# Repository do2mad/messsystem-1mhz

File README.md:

# Messsystem 6× DC + 1× AC

Ein kleines Messgerät für den Reparaturplatz: Es überwacht **sechs
Gleichspannungen (0–30 V)** und **eine Wechselspannung (9 V~)** gleichzeitig
und zeigt sie auf einem **20×4-LCD** an. Entstanden ist es, um die
Spannungsschienen eines Commodore-64 , Pet oder andere in einem Blick zu prüfen —
es passt aber auf jedes Gerät mit mehreren Versorgungsspannungen.

Projektseite und Diskussion: <https://1mhz.de>

*Startbild mit Firmware-Version. Unten die Eingänge: +5 V/GND/AC, DC1–DC6 als Klemmen und DC6 zusätzlich an 2-mm-Bananenbuchsen (J16).*

*Im Betrieb: zwei belegte Kanäle, die übrigen ausgeblendet. Rechts unten zeigt `UEBERW`, dass die Grenzwert-Überwachung aktiv ist.*

## Was es kann

- **7 Kanäle an einem ADC**: ein CD4051 schaltet die Eingänge auf einen
  einzigen ADC-Pin, ein MCP6004-Spannungsfolger entkoppelt den hochohmigen
  Teiler vom Sample-and-Hold.
- **Grenzwert-Überwachung**: Ein funktionierendes Gerät anschließen, Taste
  halten, Toleranz wählen — fertig. Fällt am Prüfling eine Schiene aus dem
  Bereich, meldet sich das Gerät mit Ton, blinkendem Hintergrundlicht und
  einem blinkenden Kanal im Display.
- **Kalibrierung mit zwei Punkten pro Kanal**, im EEPROM gespeichert.
- **Datenaufzeichnung** als CSV über die serielle Schnittstelle, mit
  Semikolon und Dezimalkomma — direkt in der Tabellenkalkulation brauchbar.
- **Serielle Konsole** für Kalibrierung, Grenzwerte und Diagnose.

## Technik in Stichworten

| | |
|---|---|
| MCU | ATmega328P, interner 8-MHz-Oszillator, kein Quarz |
| Multiplexer | CD4051 (8:1) auf ADC0 (PC0) |
| Puffer | MCP6004 (Rail-to-Rail, pinkompatibel zum LM324, **max. 6 V**) |
| Referenz | LM4040 4,096 V an AREF |
| Anzeige | HD44780 20×4, parallel im 4-Bit-Modus |
| DC-Eingänge | Teiler 1 MΩ / 100 kΩ (≈1:11), 100 nF, bipolare 1N4148-Klemme |
| AC-Eingang | Brückengleichrichter, Teiler 470 k / 150 k, Mittelwert → `Vrms = MW / 0,9` |
| Alarm | passiver Piezo (Reichelt EPM 121, 4 kHz) gegentaktig an PB6/PB7 über 330 Ω; Hintergrundlicht über Q1 (2N7000) an PB3 |
| Versorgung | 5 V über J9 oder USB-Mini J10 (nur eine Quelle gleichzeitig, kein Verpolschutz) |

## Bedienung

**Taster SW1 im Betrieb**

| Aktion | Wirkung |
|---|---|
| kurz tippen | Alarm stumm, bis er vorbei ist |
| ≥ 2 s halten | Grenzen einrichten, startet bei ± 1 % |
| im Einrichten tippen | Toleranz +1 % je Tipp (1…20, dann wieder 1) |
| im Einrichten 5 s warten | einlernen mit der gezeigten Toleranz, Wert wird gespeichert |
| ≥ 6 s halten | alle Grenzen löschen |
| beim Einschalten halten | Kalibriermodus |

Das Statusfeld unten rechts zeigt `UEBERW`, `ALARM!`, `STUMM`, beim Halten
`SETUP` bzw. `LOESCH` und im Einrichten die Toleranz, etwa `+- 7%`.

**Summer dauerhaft aus:** Jumper am ISP-Stecker J18 über Pin 1 und 3
(MISO gegen SCK). Zum Programmieren muss er ohnehin herunter.

**Serielle Konsole** (9600 Baud, `?` zeigt die Liste):
`l` Aufzeichnung · `r` Rohwerte · `s` Stopp · `1`–`6` / `a` kalibrieren ·
`g` / `G` Grenzen anzeigen/setzen · `e` einlernen · `t` Toleranz ·
`x` löschen · `m` stumm · `b` Summer-Test

## Firmware bauen und flashen

Arduino-IDE mit **MiniCore**: Board „ATmega328", Variante 328P,
Clock **Internal 8 MHz**, *No bootloader* → „Kompilierte Binärdatei
exportieren". Bibliothek `LiquidCrystal` ist im Core enthalten.

Fuses beim Brennen (z. B. TL866-II Plus, Xgpro, ATMEGA328P@DIP28):

```
Low = 0xE2    High = 0xD9    Ext = 0xFF   (0xFD für Brown-out 2,7 V)
```

Nach dem ersten Flashen einmal kalibrieren: beim Einschalten den Taster
gedrückt halten.

## Hardware

Das KiCad-Projekt liegt unter `hardware/kicad/` und bringt **alle benutzten
Symbole und Footprints als Projektbibliothek** mit (`libs/`, eingebunden über
`sym-lib-table` und `fp-lib-table`). Es lässt sich also ohne zusätzliche
Bibliotheken öffnen und bearbeiten. KiCad 10.

Die 3D-Modelle liegen vollständig in `hardware/kicad/packages3D/` – die
3D-Ansicht (Alt+3) ist nach dem Klonen sofort komplett, ohne weitere
Downloads.

Stückliste: `hardware/BOM.md` (mit Erklärungen) und `hardware/BOM.csv`.

## Stand

Aufgebaut, bestückt und im Einsatz. Die Versionsgeschichte mit allen
Entscheidungen, Messungen und Fallstricken steht in `CHANGELOG.md` —
auch die Geschichte vom gefälschten LM4040.

## Lizenz

MIT, siehe `LICENSE`. Nachbau, Änderung und Weitergabe sind ausdrücklich
erwünscht — über eine Rückmeldung im Forum freue ich mich.

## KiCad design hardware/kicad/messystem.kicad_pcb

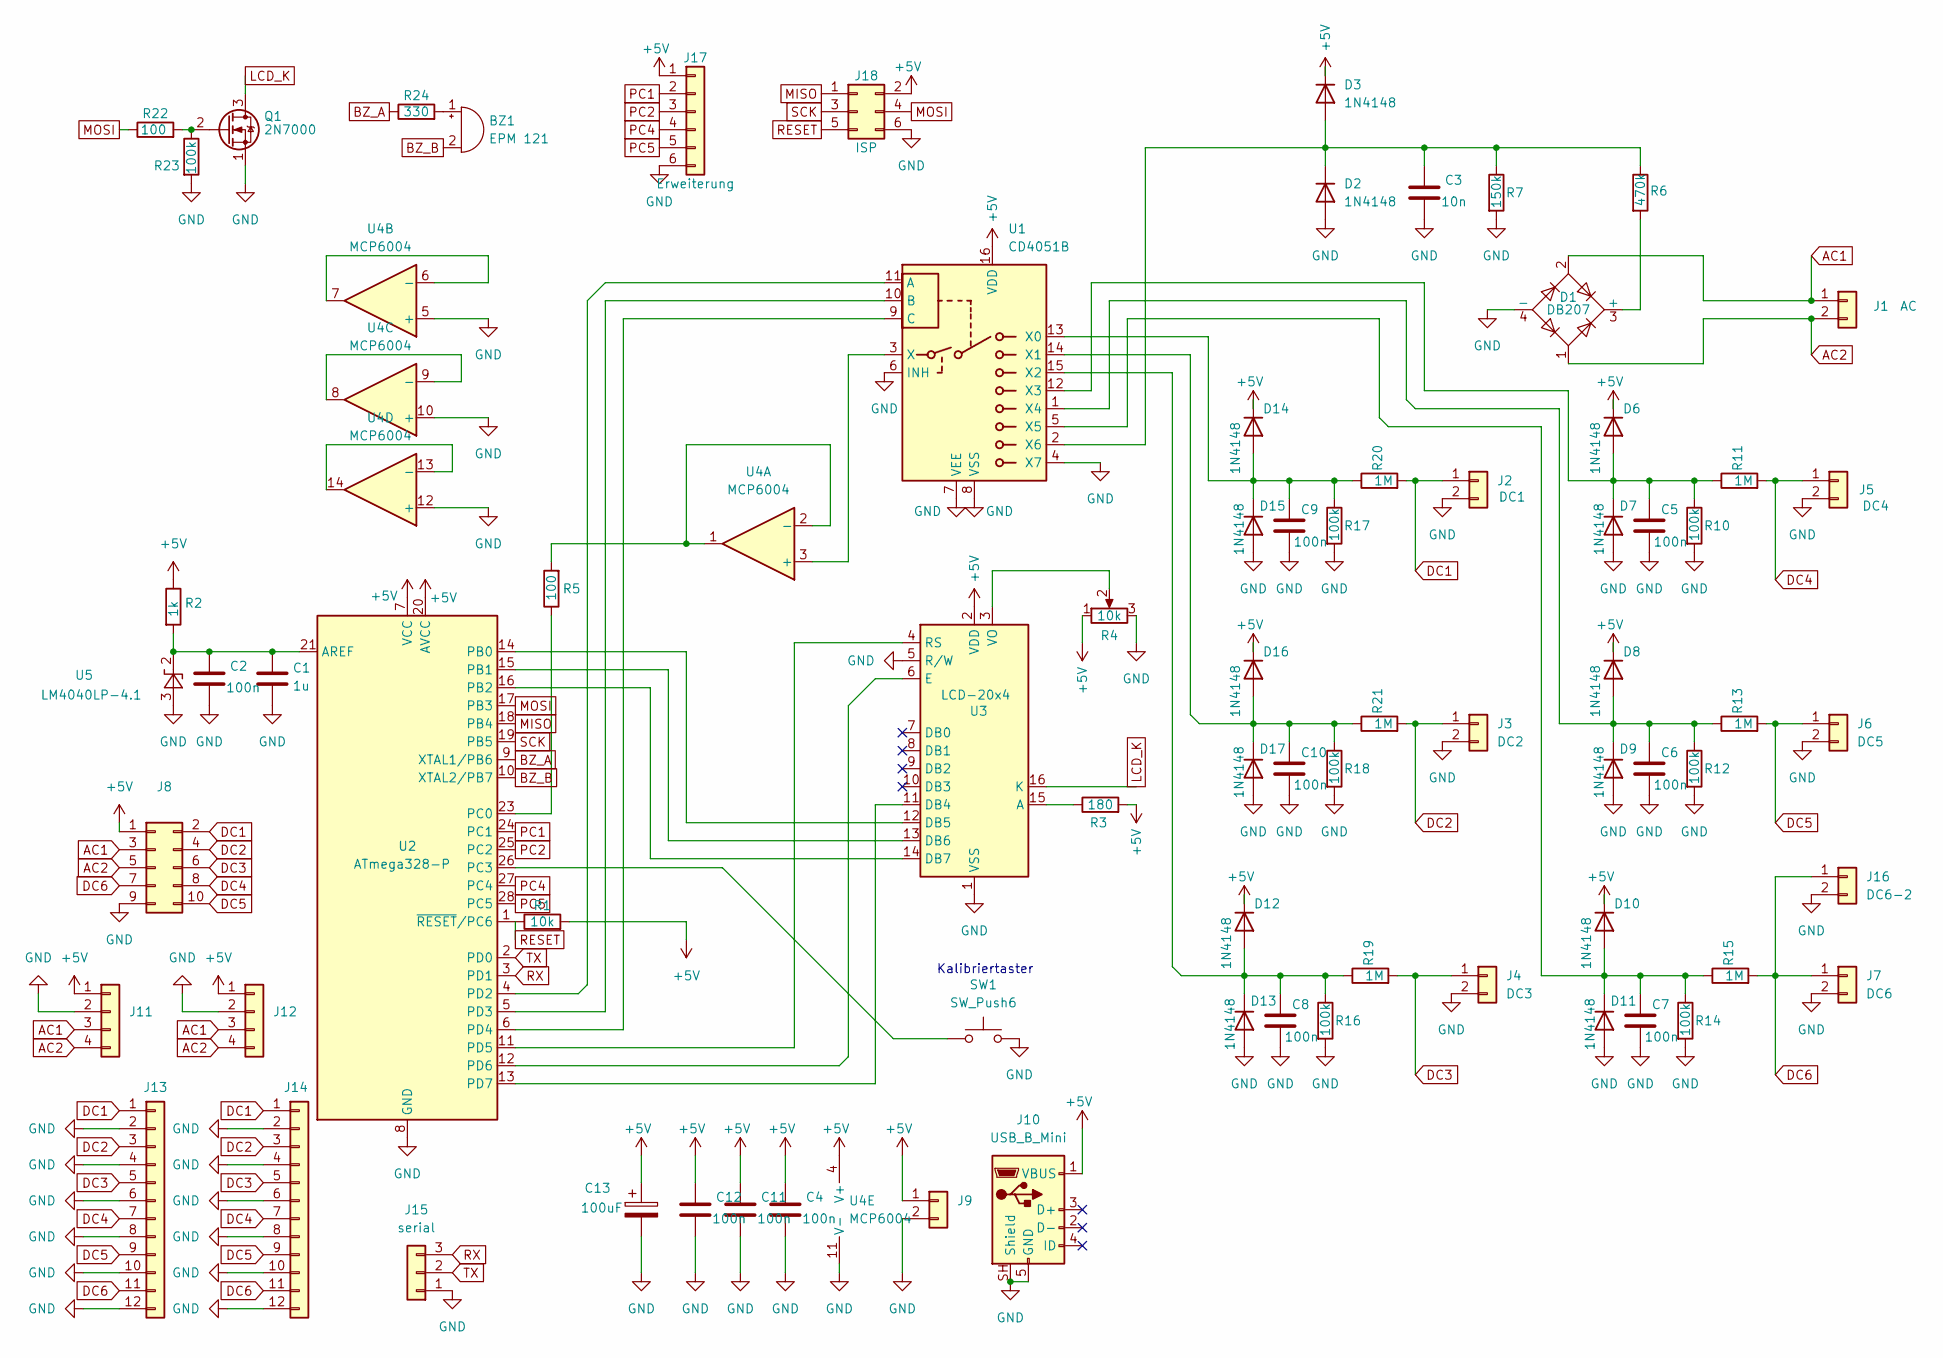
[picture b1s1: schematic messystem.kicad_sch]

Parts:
BZ1: EPM 121; Buzzer_12x9.5RM7.6
C1: 1u; C_MAD
C2, C4, C5, C6, C7, C8, C9, C10, C11, C12: 100n; C_MAD
C3: 10n; C_MAD
C13: 100uF; Elko_Mad
D1: DB207; Diode_Bridge_DIP-4_W7.62mm_P5.08mm
D2, D3, D6, D7, D8, D9, D10, D11, D12, D13, D14, D15, D16, D17: 1N4148; D_DO-35_SOD27_P7.62mm_Horizontal
J1: AC; PinHeader_1x02_P2.54mm_Vertical-MAD
J2: DC1; PinHeader_1x02_P2.54mm_Vertical-MAD
J3: DC2; PinHeader_1x02_P2.54mm_Vertical-MAD
J4: DC3; PinHeader_1x02_P2.54mm_Vertical-MAD
J5: DC4; PinHeader_1x02_P2.54mm_Vertical-MAD
J6: DC5; PinHeader_1x02_P2.54mm_Vertical-MAD
J7: DC6; PinHeader_1x02_P2.54mm_Vertical-MAD
J8: Conn_02x05_Odd_Even; IDC-Header_2x05_P2.54mm_Horizontal
J9: 5V; PinHeader_1x02_P2.54mm_Vertical-MAD
J10: USB_B_Mini; USB_Mini-B_horizontal
J11, J12: 5V/AC; PinSocket_1x04_P2.54mm_Vertical
J13, J14: DC1-DC6; PinSocket_1x12_P2.54mm_Vertical
J15: serial; PinSocket_1x03_P2.54mm_Vertical
J16: DC6-2; 2mm-banane
J17: Erweiterung; PinHeader_1x06_P2.54mm_Vertical
J18: ISP; PinHeader_2x03_P2.54mm_Vertical
Q1: 2N7000; TO-92_Inline
R1: 10k; R_Axial_DIN0204_L3.6mm_D1.6mm_P7.62mm_Horizontal
R2: 1k; R_Axial_DIN0204_L3.6mm_D1.6mm_P7.62mm_Horizontal
R3: 180; R_Axial_DIN0204_L3.6mm_D1.6mm_P7.62mm_Horizontal
R4: 10k; Potentiometer_Bourns_3296W_Vertical
R5, R22: 100; R_Axial_DIN0204_L3.6mm_D1.6mm_P7.62mm_Horizontal
R6: 470k; R_Axial_DIN0204_L3.6mm_D1.6mm_P7.62mm_Horizontal
R7: 150k; R_Axial_DIN0204_L3.6mm_D1.6mm_P7.62mm_Horizontal
R10, R12, R14, R16, R17, R18, R23: 100k; R_Axial_DIN0204_L3.6mm_D1.6mm_P7.62mm_Horizontal
R11, R13, R15, R19, R20, R21: 1M; R_Axial_DIN0204_L3.6mm_D1.6mm_P7.62mm_Horizontal
R24: 330; R_Axial_DIN0204_L3.6mm_D1.6mm_P7.62mm_Horizontal
SW1: SW_Push6; SW_Tactile_SPST_Angled_PTS645Vx39-2LFS
U1: CD4051B; DIP-16_W7.62mm_Socket_LongPads
U2: ATmega328-P; DIP-28_W7.62mm
U3: LCD-20x4
U4: MCP6004; DIP-14_W7.62mm_LongPads
U5: LM4040LP-4.1; TO-92_Inline

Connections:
+5V: C4.1, C11.1, C12.1, C13.1, D3.1 (K), D6.1 (K), D8.1 (K), D10.1 (K), D12.1 (K), D14.1 (K), D16.1 (K), J8.1, J9.1, J10.1 (VBUS), J11.1, J12.1, J17.1, J18.2, R1.2, R2.1, R3.2, R4.1, U1.16 (VDD), U2.7 (VCC), U2.20 (AVCC), U3.2 (VDD), U4.4 (V+)
AC1: D1.2, J1.1, J8.3, J11.3, J12.3
AC2: D1.1, J1.2, J8.5, J11.4, J12.4
BZ_A: R24.1, U2.9 (XTAL1/PB6)
BZ_B: BZ1.2 (-), U2.10 (XTAL2/PB7)
DC1: J2.1, J8.2, J13.1, J14.1, R20.2
DC2: J3.1, J8.4, J13.3, J14.3, R21.2
DC3: J4.1, J8.6, J13.5, J14.5, R19.2
DC4: J5.1, J8.8, J13.7, J14.7, R11.2
DC5: J6.1, J8.10, J13.9, J14.9, R13.2
DC6: J7.1, J8.7, J13.11, J14.11, J16.1, R15.2
GND: C1.2, C2.2, C3.2, C4.2, C5.2, C6.2, C7.2, C8.2, C9.2, C10.2, C11.2, C12.2, C13.2, D1.4 (-), D2.2 (A), D7.2 (A), D9.2 (A), D11.2 (A), D13.2 (A), D15.2 (A), D17.2 (A), J2.2, J3.2, J4.2, J5.2, J6.2, J7.2, J8.9, J9.2, J10.5 (GND), J10.SH (Shield), J11.2, J12.2, J13.2, J13.4, J13.6, J13.8, J13.10, J13.12, J14.2, J14.4, J14.6, J14.8, J14.10, J14.12, J15.1, J16.2, J17.6, J18.6, Q1.1 (S), R4.3, R7.2, R10.2, R12.2, R14.2, R16.2, R17.2, R18.2, R23.2, SW1.2, U1.4 (X7), U1.6 (INH), U1.7 (VEE), U1.8 (VSS), U2.8 (GND), U2.22 (GND), U3.1 (VSS), U3.5 (R/W), U3.17, U3.18, U3.19, U3.20, U4.5 (+), U4.10 (+), U4.11 (V-), U4.12 (+), U5.3 (A)
LCD_K: Q1.3 (D), U3.16 (K)
MISO: J18.1, U2.18 (PB4)
MOSI: J18.4, R22.1, U2.17 (PB3)
unnamed: BZ1.1 (+), R24.2
unnamed: D1.3 (+), R6.2
unnamed: C3.1, D2.1 (K), D3.2 (A), R6.1, R7.1, U1.2 (X6)
unnamed: C5.1, D6.2 (A), D7.1 (K), R10.1, R11.1, U1.12 (X3)
unnamed: C6.1, D8.2 (A), D9.1 (K), R12.1, R13.1, U1.1 (X4)
unnamed: C7.1, D10.2 (A), D11.1 (K), R14.1, R15.1, U1.5 (X5)
unnamed: C8.1, D12.2 (A), D13.1 (K), R16.1, R19.1, U1.15 (X2)
unnamed: C9.1, D14.2 (A), D15.1 (K), R17.1, R20.1, U1.13 (X0)
unnamed: C10.1, D16.2 (A), D17.1 (K), R18.1, R21.1, U1.14 (X1)
unnamed: Q1.2 (G), R22.2, R23.1
unnamed: U1.11 (A), U2.4 (PD2)
unnamed: U1.10 (B), U2.5 (PD3)
unnamed: U1.9 (C), U2.6 (PD4)
unnamed: U1.3 (X), U4.3 (+)
unnamed: C1.1, C2.1, R2.2, U2.21 (AREF), U5.2 (K)
unnamed: U2.14 (PB0), U3.12 (DB5)
unnamed: U2.15 (PB1), U3.13 (DB6)
unnamed: U2.16 (PB2), U3.14 (DB7)
unnamed: R5.1, U2.23 (PC0)
unnamed: SW1.1, U2.26 (PC3)
unnamed: U2.11 (PD5), U3.4 (RS)
unnamed: U2.12 (PD6), U3.6 (E)
unnamed: U2.13 (PD7), U3.11 (DB4)
unnamed: R3.1, U3.15 (A)
unnamed: R4.2, U3.3 (VO)
unnamed: R5.2, U4.1, U4.2 (-)
unnamed: U4.6 (-), U4.7
unnamed: U4.8, U4.9 (-)
unnamed: U4.13 (-), U4.14
PC1: J17.2, U2.24 (PC1)
PC2: J17.3, U2.25 (PC2)
PC4: J17.4, U2.27 (PC4)
PC5: J17.5, U2.28 (PC5)
RESET: J18.5, R1.1, U2.1 (~RESET/PC6)
RX: J15.3, U2.3 (PD1)
SCK: J18.3, U2.19 (PB5)
TX: J15.2, U2.2 (PD0)

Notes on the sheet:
Kalibriertaster

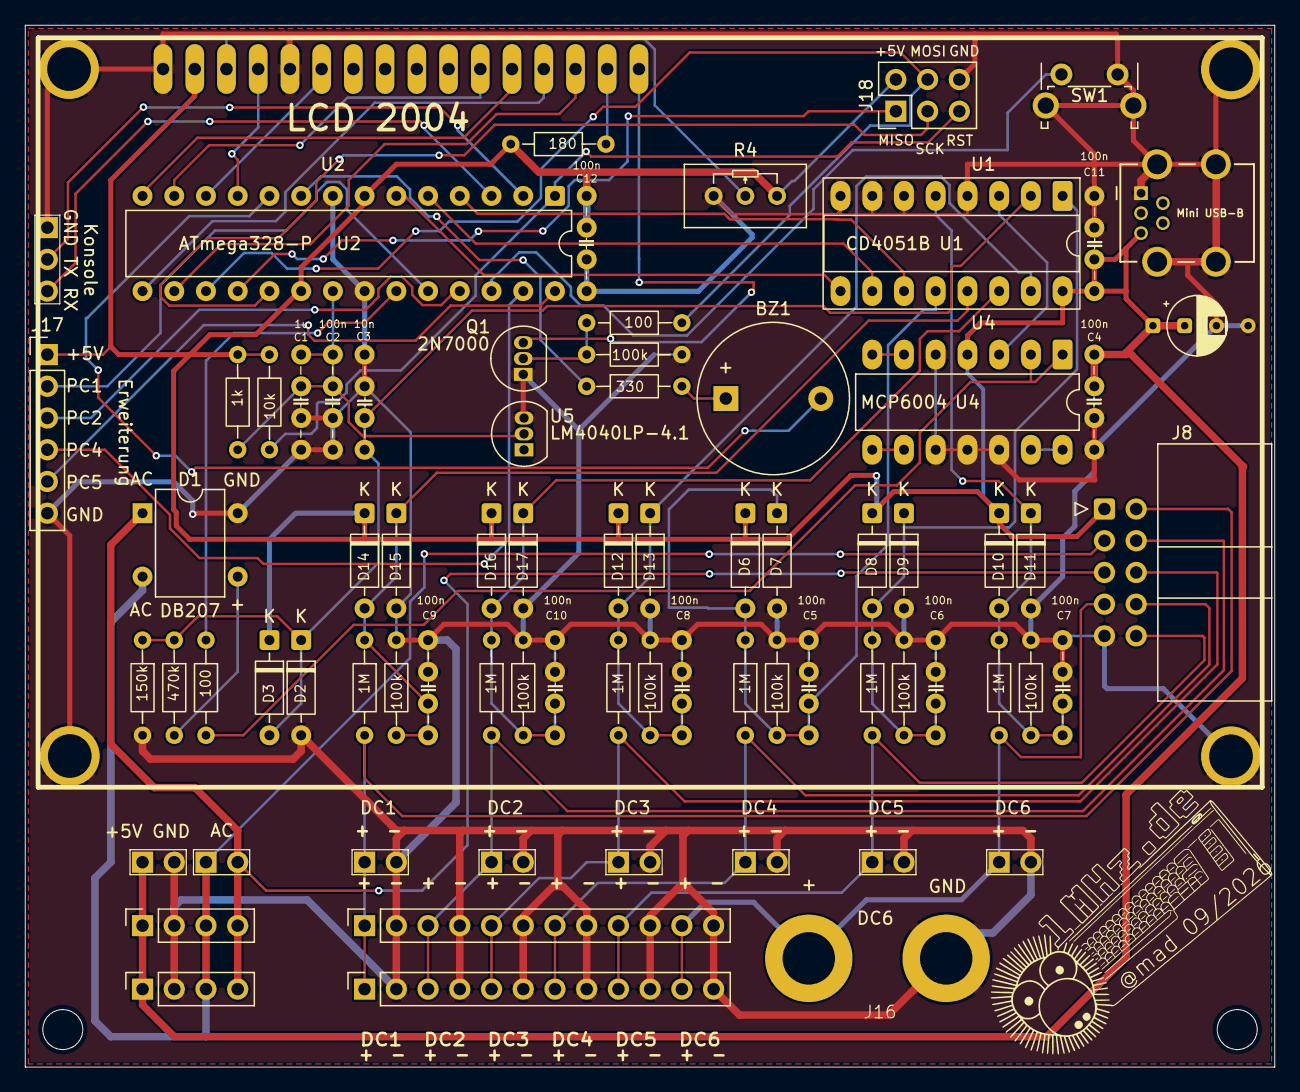
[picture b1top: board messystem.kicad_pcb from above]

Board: 2 copper layers, 100.0 x 83.4 mm, 78 parts (1 on the bottom side), 52 nets.

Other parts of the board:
1MHZ, 1MHZ.de: LOGO; 1MHzLogo25

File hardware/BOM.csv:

Menge;Bezeichner;Bauteil;Wert;Gehaeuse;Funktion
1;U1;CD4051BE;;DIP-16;8:1 Analog-Mux
1;U2;ATmega328P-PU;;DIP-28;MCU (int. 8 MHz)
1;U3;LCD 20x4 HD44780;;Modul parallel;Display + 16-pol Leiste
1;U4;MCP6004;;DIP-14;Quad-OpAmp RRIO, Sektion A = Follower, max. 6 V
1;U5;LM4040DIZ-4.1;4,096 V;TO-92;Spannungsreferenz (Test: LM4040-2.5)
1;D1;Brueckengleichrichter;;KONFLIKT;Value MB6S (SOP-4) vs. Footprint Diode_Bridge_DIP-4 - klaeren
14;D2,D3,D6-D17;1N4148;;DO-35;bipolare Klemmdioden (2x je Kanal)
1;R1;Widerstand;10k;0207;Reset-Pullup
1;R2;Widerstand;1k;0207;Vorwiderstand Referenz U5
1;R3;Widerstand;180R;0207;LCD-Backlight
1;R4;Trimmpoti;10k;Bourns 3296W stehend;LCD-Kontrast
1;R5;Widerstand;100R;0207;Serie OpAmp->ADC
1;R6;Widerstand;470k;0207;AC-Teiler oben
1;R7;Widerstand;150k;0207;AC-Teiler unten
6;R11,R13,R15,R19,R20,R21;Widerstand;1M;0207;DC-Teiler oben
6;R10,R12,R14,R16,R17,R18;Widerstand;100k;0207;DC-Teiler unten
1;C1;Keramik/Folie;1u;RM5;VREF-Filter
1;C2;Keramik;100n;RM5;VREF-Filter (nah an AREF)
1;C3;Keramik;10n;RM5;AC-Knoten (nicht vergroessern)
6;C5,C6,C7,C8,C9,C10;Keramik X7R;100n;RM5;DC-Teilerknoten
3;C4,C11,C12;Keramik;100n;RM5;Abblockung U1/U2/U4
1;C13;Elko;100u;RM2,5;Stuetzkondensator +5V
1;J1;Bananenbuchse 2mm (2x);;RM2,54;AC-Eingang 9V~
6;J2-J7;Bananenbuchse 2mm (je 2x);;RM2,54;DC1-DC6 - Plus links anordnen
1;J8;IDC-Wanne 2x05;;RM2,54;Sammelstecker (parallel zu J1-J7)
1;J9;Stiftleiste 1x02;;RM2,54;+5V Einspeisung
1;J10;USB-Mini-B Buchse;;liegend;+5V Einspeisung (VBUS/GND/Schirm)
2;J13,J14;Buchsenleiste 1x12;DC1-DC6;RM2,54;Signal links + GND rechts je Kanal
2;J11,J12;Buchsenleiste 1x04;5V/AC;RM2,54;+5V,GND,AC1,AC2
1;J15;Stiftleiste 1x03;serial;RM2,54;1=GND 2=TX(PD1) 3=RX(PD0)
1;J16;Bananenbuchse 2mm (2x);DC6-2;RM2,54;zweiter Abgriff fuer DC6
1;SW1;Taster (Schliesser);;Kurzhub;Kalibrierung PC3->GND
1;-;IC-Sockel-Set;;DIP-28/16/14;optional
1;Q1;2N7000;;TO-92;LCD-Licht schalten (V1.1)
1;R22;Widerstand;100R;0207;Gate Q1 (V1.1)
1;R23;Widerstand;100k;0207;Gate-Pulldown Q1 (V1.1)
1;R24;Widerstand;330R;0207;Summer (V1.1)
1;BZ1;Piezo passiv Reichelt EPM 121;EPM 121;12mm;Alarmton an PB6/PB7, 4 kHz (V1.1)
1;J17;Stiftleiste 1x06;;RM2,54;Erweiterung +5V/PC1/PC2/PC4/PC5/GND (V1.1)
1;J18;Stiftleiste 2x03;;RM2,54;ISP (V1.1)

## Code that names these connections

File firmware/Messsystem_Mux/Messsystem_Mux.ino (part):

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 *  Version 1.1  (09.2026)
 *
 *  MCU  : ATmega328P @ 8 MHz (interner Oszillator), interner 10-bit-ADC
 *  Mux  : CD4051 (8:1) -> 7 Signale auf EINEN ADC-Pin (PC0/ADC0/A0)
 *  Puffer: MCP6004-Spannungsfolger hinter dem Mux (Rail-to-Rail, pinkompatibel
 *          zum LM324, max. 6 V Betriebsspannung) -> ADC-Quelle niederohmig
 *  LCD  : 20x4, HD44780 DIREKT (parallel, 4-bit) - kein I2C-Modul
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 *  der Kanal mit Alarm blinkt im Display mit (Wert <-> "ALARM").
 *
 *  NEU in V1.1 (Vorschlaege aus dem Forum, Thread 8687):
 *   - Hintergrundlicht ueber Q1 (2N7000) an PB3 -> blinkt bei Alarm
 *   - Piezo-Summer BZ1 (passiv, Reichelt EPM 121, 4 kHz), gegentaktig
 *     zwischen PB6 und PB7 ueber R24 330R
 *   - Grenzwert-Ueberwachung pro Kanal, Einlernen per Taste
 *   - Datenaufzeichnung (CSV) ueber die serielle Schnittstelle (J15)
 *  Laeuft auch auf der Beta-Platine ohne Q1/Summer: die Zusatzpins sind
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 *  Der zuletzt benutzte Prozentwert steht im EEPROM.
 *
 *  Summer dauerhaft stumm: Jumper am ISP-Stecker J18 ueber Pin 1 und 3
 *  (MISO/PB4 gegen SCK/PB5, das fest auf Low liegt). Jumper gesteckt =
 *  kein Ton; das Lichtblinken bei Alarm bleibt. Zum Programmieren muss
 *  der Jumper ab, sonst sind MISO und SCK kurzgeschlossen.
 *
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 *
 *  Mux-Kanaele (CD4051 X0..X7):
 *     0..5 = DC1..DC6      6 = AC (gleichgerichtet)      7 = frei (GND)
 *  Select: A=PD2, B=PD3, C=PD4   (A = LSB)
 *
 *  Arduino-IDE:
 *    Board : "ATmega328" (MiniCore) -> Clock: Internal 8 MHz
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#include <LiquidCrystal.h>   // parallel HD44780 (4-bit), im Core enthalten
#include <EEPROM.h>            // Kalibrier- und Grenzwerte dauerhaft speichern

// LCD parallel: RS,E,D4,D5,D6,D7  =  D5,D6,D7,D8,D9,D10  (PD5,PD6,PD7,PB0,PB1,PB2)
LiquidCrystal lcd(5, 6, 7, 8, 9, 10);

#define CAL_BUTTON A3   // Taster SW1 gegen GND (PC3 / Pin 26), interner Pull-up

// ---- Mux-Steuerpins -------------------------------------------------
#define MUX_A  2      // PD2  (LSB)
#define MUX_B  3      // PD3
#define MUX_C  4      // PD4
#define ADC_PIN A0    // PC0 = Pufferausgang (U4A) -> ADC0

#define CH_AC   6     // Mux-Kanal des AC-Zweigs
#define N_CH    7     // 6x DC + AC  (Index 0..5 = DC1..DC6, 6 = AC)

// ---- NEU V1.1: Hintergrundlicht und Summer --------------------------
#define BL_PIN        11      // PB3 (Pin 17) -> R22 100R -> Gate Q1 (2N7000)
                              // Q1 schaltet LCD-Kathode (K, Pin 16) nach GND
#define BL_BRIGHT    255      // Helligkeit normal (0..255, PWM ueber Timer2)
#define BL_ALARM_LOW   0      // Helligkeit in der dunklen Blinkphase
// Passiver Piezo (Reichelt EPM 121) gegentaktig zwischen PB6 (Pin 9) und PB7 (Pin 10), in Reihe
// R24 330R. Ton kommt aus dem Timer1-Interrupt -> blockiert die Messung nicht.
#define BUZ_FREQ    4000UL    // Hz; Resonanz des EPM 121 = 4 kHz -> am lautesten

// ---- NEU V1.2: Summer per Jumper stumm schalten ----------------------
// Direkt ueber die Portregister (PB4/PB5), damit die Pin-Nummerierung des
// gewaehlten Cores keine Rolle spielt:
//   PB4/MISO (IC-Pin 18) = J18 Pin 1, Eingang mit internem Pull-up
//   PB5/SCK  (IC-Pin 19) = J18 Pin 3, Ausgang fest auf Low (Masse fuer den Jumper)
                               // Jumper ueber J18 Pin 1 und 3 = Summer aus
                               // (die beiden Pins liegen nebeneinander).
                               // Das Lichtblinken bei Alarm bleibt.
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float rawChannel(uint8_t ch, uint16_t n) { setMux(ch); return readAvg(n); }

// =====================================================================
//  Summer: Timer1 im CTC-Modus, der Interrupt toggelt PB6 und PB7
//  gegenphasig -> doppelte Spannung am Piezo, ohne Transistor.
// =====================================================================
ISR(TIMER1_COMPA_vect) {
  PINB = _BV(PB6) | _BV(PB7);        // Schreiben auf PINx toggelt die Pins (atomar)
}

// NEU V1.2: Jumper an J17 gesteckt -> Summer bleibt stumm (Licht blinkt weiter)
bool buzMutedByJumper() { return !(PINB & _BV(PB4)); }

void buzInit() {
  DDRB  &= ~_BV(PB4);  PORTB |=  _BV(PB4);   // MISO: Eingang mit Pull-up
  DDRB  |=  _BV(PB5);  PORTB &= ~_BV(PB5);   // SCK : Ausgang fest Low
  DDRB  |=  _BV(PB6) | _BV(PB7);
  PORTB &= ~(_BV(PB6) | _BV(PB7));
  TIMSK1 = 0;
  TCCR1A = 0;
  TCCR1B = _BV(WGM12) | _BV(CS11);   // CTC, Prescaler 8
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void beep(uint16_t ms) {
  if (buzMutedByJumper()) return;         // NEU V1.2: Jumper = kein Ton
  uint8_t s = SREG; cli();
  PORTB = (PORTB & ~_BV(PB7)) | _BV(PB6);   // Startzustand gegenphasig
  TCNT1  = 0;
  TIFR1  = _BV(OCF1A);
  TIMSK1 = _BV(OCIE1A);
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void buzStop() {
  uint8_t s = SREG; cli();
  TIMSK1 = 0;
  PORTB &= ~(_BV(PB6) | _BV(PB7));   // beide low -> keine Gleichspannung am Piezo
  SREG = s;
  buzOn = false;
}
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}

// =====================================================================
//  Taster im Betrieb: Pin-Change-Interrupt an PC3 misst die Haltedauer,
//  damit auch kurze Tipper waehrend einer Messung nicht verloren gehen.
// =====================================================================
ISR(PCINT1_vect) {
  bool down = !(PINC & _BV(PC3));
  unsigned long now = millis();
  if (down && !btnHeld) { btnHeld = true; btnT0 = now; }
  else if (!down && btnHeld) {
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}

void btnInit() {
  PCMSK1 |= _BV(PCINT11);            // PC3
  PCIFR   = _BV(PCIF1);
  PCICR  |= _BV(PCIE1);
}
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  Serial.print(F("Toleranz: +-")); Serial.print(limPct);
  Serial.print(F(" %   Summer: "));
  Serial.print(buzMutedByJumper() ? F("per Jumper AUS") : F("an"));
  Serial.print(F("   (PB4=")); Serial.print((PINB & _BV(PB4)) ? '1' : '0');
  Serial.println(F(")"));
}

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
